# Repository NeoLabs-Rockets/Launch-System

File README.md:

<div align="center">

# NeoLabs-Rockets Launch System

**Rocket systems by NeoLabs — ESP32 launch controller + Node.js mission dashboard.**

---

[🚀 Mission Dashboard](#mission-dashboard) · [🛰️ Launch System](#launch-system)

[Compatible with NeoLabs-Rockets launch platform](https://github.com/NeoLabs-Rockets/Launch-Platform)

---

</div>

## Mission Dashboard

A single-page web app that runs on a laptop at the launch site and connects to a custom PCB over Bluetooth (BLE).

### Features

| Feature | Description |
|---------|-------------|
| **Launch Console** | Guided 4-step wizard: Connect → Checklist → Arm → Countdown. BLE connects once and drives every view. |
| **Live BLE keepalive** | Active ping every 2 s detects silent drops; heartbeat during countdown proves the link every 700 ms. |
| **Weather & airspace** | Live wind, temperature, precipitation, and ADS-B aircraft corridor check with GO / HOLD / NO-GO badge. |
| **Location Finder** | OSM-based candidate scorer — rates grid points against roads, highways (big exclusion), settlements, power lines, water, trees, airports, and open fields. Green-only results on the map; links open Google Earth satellite view. |
| **Camera overlay** | Cinematic broadcast HUD with live T−countdown ring (bottom-right), T+ elapsed after ignition, BLE and weather telemetry. |
| **Cross-device camera** | Phone subscribes to the laptop's SSE stream and receives the countdown + BLE state in real time — no BLE on the phone needed. |

---

## Launch System

BLE launch controller — see [`/LaunchSystem`](LaunchSystem/).

One-layer PCB - no bridges

---

<div align="center">

*Made with ❤️ by [Neo](https://github.com/neooriginal) · [NeoLabs Systems](https://github.com/NeoLabs-Systems)*

</div>

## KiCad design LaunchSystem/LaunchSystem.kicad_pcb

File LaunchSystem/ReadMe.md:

# NeoLabs Rockets â€” ESP32 Mission Control

BLE-controlled trigger/relay switch built on an ESP32. The board exposes only a
Bluetooth Low Energy launch service; the Mission Dashboard provides the shared
**arm â†’ launch** workflow. Designed to run off a portable power supply.

> Firmware: [`Arduino/ESP32_AP_Trigger/ESP32_AP_Trigger.ino`](Arduino/ESP32_AP_Trigger/ESP32_AP_Trigger.ino)
>
> Web Bluetooth requires a Chromium-family browser such as Chrome or Edge on
> localhost/HTTPS. Firefox and Safari do not currently support this control path.

The controller intentionally starts no WiFi access point and serves no embedded
web UI. One authorized dashboard owns BLE while other dashboards synchronize
through the Mission Dashboard server.

## Arduino compile settings

Install the **NimBLE-Arduino** library from the Arduino Library Manager before
compiling. The sketch uses NimBLE instead of the default ESP32 BLE stack because
it is smaller and well suited to the BLE-only controller.

Recommended Arduino IDE board settings:

| Setting | Value |
|---------|-------|
| Board | ESP32 Dev Module or your exact ESP32 board |
| Partition Scheme | Default works; Huge APP (3MB No OTA) gives more headroom |
| Core Debug Level | None |

The current BLE-only sketch compiles on the default ESP32 Dev Module partition
with NimBLE-Arduino installed. If future features push it over the limit, change
**Tools -> Partition Scheme** to a larger APP partition such as
**Huge APP (3MB No OTA)**.

## Features

- **BLE only** â€” no ESP32 WiFi access point, captive portal, embedded UI, or REST API.
- **Checklist-gated arming** â€” every safety item must be acknowledged before arming.
- **Join authorization** â€” the code exists only in ESP32 firmware. The first BLE-owning
  dashboard needs no code; additional dashboards are verified by the ESP32 through the owner.
- **Lockout** â€” after **10** wrong codes the system locks out until reboot
  (counter is kept in RAM only, so a power cycle clears it).
- **Arm/Disarm safety** â€” the trigger is disabled until the system is armed.
  Auto-disarms after every shot.
- **Launch sequence** â€” 10 s countdown with English browser TTS; says
  *"Ignition"* at zero, then drives the output **HIGH 500 ms later**.
- **Trigger pulse** — non-blocking HIGH pulse on the trigger pin, then back LOW.
- **Status LED** â€” solid while armed, 5 Hz blink while firing.
- **Vibration motor** — distinct haptic patterns for arm, disarm, wrong code, lockout, countdown start, final-second ticks, abort, link-lost safety stop, and ignition. No idle buzz.
- **Physical ARM button** (optional, disabled by default) â€” toggles arm state in hardware.
- **Shared dashboard control** â€” one BLE owner, with status and commands relayed to authorized devices.

## Pin assignments

These are defined at the top of the sketch and are the only place you should
change them:

| Function          | GPIO | Direction        | Notes |
|-------------------|------|------------------|-------|
| **Trigger out**   | `26` | OUTPUT           | Goes HIGH for 2000 ms on launch â†’ relay IN / driver |
| **Status LED**    | `2`  | OUTPUT           | Onboard LED on most DevKits. Set to `-1` to disable |
| **Vibration motor**| `23`| OUTPUT           | Motor **(+)** â†’ GPIO 23, **(â€“)** â†’ GND. Set to `-1` to disable |
| **Physical ARM**  | `25` | INPUT_PULLUP     | Momentary button to **GND** (LOW = pressed). `-1` = disabled (default) |

> âš ï¸ Avoid GPIO 6â€“11 (connected to the SPI flash). GPIO 26 / 25 / 23 / 2 are safe,
> standard output-capable pins on the NodeMCU DevKit.
>
> âš ï¸ Drive the motor through a transistor/MOSFET + flyback diode if it draws more
> than a few mA â€” an ESP32 GPIO can't power a motor directly. A tiny coin/ERM
> motor on a driver board is fine; bare motors need the driver.

## BLE / config

Defined near the top of the sketch:

| Setting      | Default            |
|--------------|--------------------|
| BLE name         | `NeoLabs Launch Controller` |
| Launch code      | `LAUNCH_CODE = "123456"` (stored only in ESP32 firmware) |
| Lockout         | `MAX_ATTEMPTS = 10` wrong codes â†’ locked until reboot |
| Pulse length    | `TRIGGER_MS = 2000` ms |
| Vibration       | Named patterns via `playHaptic(kind)` — non-blocking sequencer, no idle buzz |

## Parts list

| Qty | Part | Note |
|-----|------|------|
| 1 | ESP32 NodeMCU (USB-C) | diymore or similar |
| 1 | 5V 1-channel relay module (opto-isolated) | with screw terminals |
| 1 | 9V battery clip (I-type) | snap-on |
| 1 | Buck converter (9â€“12V â†’ 5V) | or LM7805 + caps |
| 1 set | Dupont jumper wires (M-M + M-F) | â€” |
| 2â€“4 | Alligator clip leads | for the output |
| 1 | Optional: toggle/momentary switch | hardware arming button |
| 1 | Optional: LED + 220Î© resistor | status / continuity |

**Approx. cost:** ~â‚¬15â€“25

## Wiring

### Power
- **9V battery +** â†’ buck converter **IN (+)**
- **9V battery â€“** â†’ buck converter **GND**
- Buck **OUT 5V** â†’ ESP32 **VIN**
- Buck **OUT GND** â†’ ESP32 **GND** + relay **GND**

### Relay control
- ESP32 **GPIO 26** (trigger out) â†’ relay **IN**
- ESP32 **GND** â†’ relay **GND**

### Optional physical ARM button
- ESP32 **GPIO 25** â†’ one leg of the button
- Other leg of the button â†’ ESP32 **GND**
  *(uses the internal pull-up; pressing pulls the pin LOW)*

### Optional status LED
- ESP32 **GPIO 2** â†’ LED **anode** â†’ 220Î© resistor â†’ ESP32 **GND**
  *(GPIO 2 already has the onboard LED on most DevKits)*

### Vibration motor
- Motor **(+)** â†’ ESP32 **GPIO 23**
- Motor **(â€“)** â†’ ESP32 **GND**
  *(For anything bigger than a tiny coin motor, drive it via a transistor/MOSFET
  with a flyback diode rather than straight off the GPIO.)*

### Load output (relay side)
- **9V battery +** â†’ relay **COM**
- Relay **NO** â†’ output alligator clip (+)
- **9V battery â€“** â†’ output alligator clip (â€“)

## REST API

Base URL: `http://192.168.4.1`

| Method | Endpoint                  | Response |
|--------|---------------------------|----------|
| `GET`  | `/api/status`             | `{ "armed", "trigger_active", "uptime_ms", "clients" }` |
| `POST` | `/api/arm?code=123456`    | `{ "ok": true, "armed": true }` â€” `401` invalid code (`attempts_left`), `423` locked out |
| `POST` | `/api/disarm`             | `{ "ok": true, "armed": false }` |
| `POST` | `/api/trigger`            | `{ "ok": true }` â€” or `403 {"ok":false,"error":"not armed"}` |
| `POST` | `/api/buzz?ms=120`        | `{ “ok”: true }` — single haptic pulse of `ms` duration |

`/api/status` also reports `locked` and `attempts_left`. Arming requires the
6-digit global password; triggering requires the system to be armed first:

```bash
curl -X POST "http://192.168.4.1/api/arm?code=123456"
curl -X POST  http://192.168.4.1/api/trigger
curl          http://192.168.4.1/api/status
```

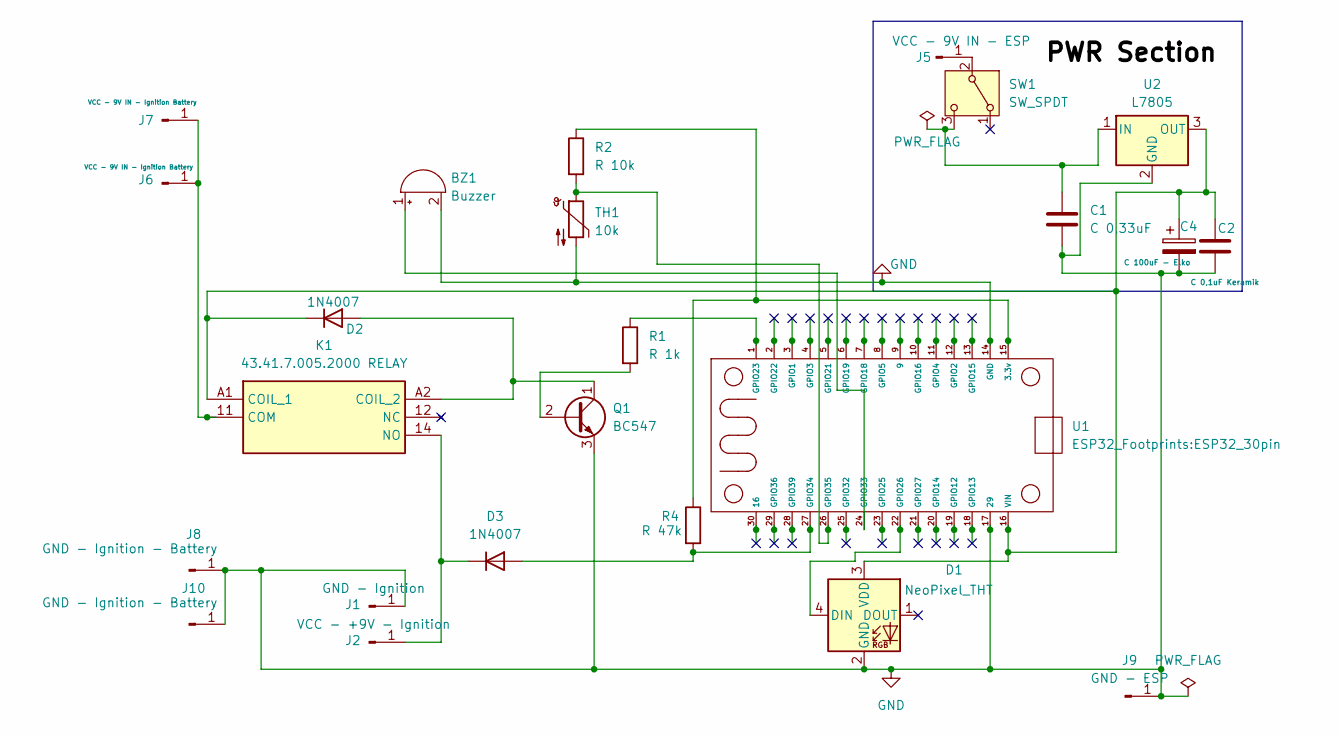
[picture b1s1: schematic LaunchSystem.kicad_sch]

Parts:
BZ1: Buzzer; Buzzer_12x9.5RM7.6
C1: C 0,33uF; C_Disc_D5.0mm_W2.5mm_P5.00mm
C2: C 0,1uF Keramik; C_Disc_D5.0mm_W2.5mm_P5.00mm
C4: C 100uF - Elko; CP_Radial_D5.0mm_P2.00mm
D1: NeoPixel_THT; LED_D5.0mm-4_RGB
D2, D3: 1N4007; D_DO-41_SOD81_P10.16mm_Horizontal
J1: GND - Ignition; TestPoint_Pad_2.0x2.0mm
J2: VCC - +9V - Ignition; TestPoint_Pad_2.0x2.0mm
J5: VCC - 9V IN - ESP; TestPoint_Pad_2.0x2.0mm
J6, J7: VCC - 9V IN - Ignition Battery; TestPoint_Pad_2.0x2.0mm
J8, J10: GND - Ignition - Battery; TestPoint_Pad_2.0x2.0mm
J9: GND - ESP; TestPoint_Pad_2.0x2.0mm
K1: 43.41.7.005.2000 RELAY; 434170052000; Manufacturer_Part_Number 43.41.7.005.2000
Q1: BC547; TO-92_Inline
R1: R 1k; R_Axial_DIN0207_L6.3mm_D2.5mm_P7.62mm_Horizontal
R2: R 10k; R_Axial_DIN0207_L6.3mm_D2.5mm_P7.62mm_Horizontal
R4: R 47k; R_Axial_DIN0207_L6.3mm_D2.5mm_P7.62mm_Horizontal
SW1: SW_SPDT; SW_SPDT_CK_JS102011SAQN
TH1: 10k; R_Axial_DIN0204_L3.6mm_D1.6mm_P2.54mm_Vertical
U1: ESP32_30pin
U2: L7805; TO-220-3_Vertical

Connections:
GND: BZ1.2 (-), C1.2, C2.2, C4.2, D1.2 (GND), J1.1 (Pin_1_1), J8.1 (Pin_1_1), J9.1 (Pin_1_1), J10.1 (Pin_1_1), Q1.3 (E), TH1.2, U1.14 (GND), U1.17 (29), U2.2 (GND)
unnamed: BZ1.1 (+), U1.24 (GPIO33)
unnamed: D1.4 (DIN), U1.22 (GPIO26)
unnamed: C2.1, C4.1, D1.3 (VDD), D2.1 (K), K1.A1 (COIL_1), U1.16 (VIN), U2.3 (OUT)
unnamed: D2.2 (A), K1.A2 (COIL_2), Q1.1 (C)
unnamed: D3.2 (A), R4.2, U1.27 (GPIO34)
unnamed: D3.1 (K), J2.1 (Pin_1_1), K1.14 (NO)
unnamed: J5.1 (Pin_1_1), SW1.2 (B)
unnamed: J6.1 (Pin_1_1), J7.1 (Pin_1_1), K1.11 (COM)
unnamed: Q1.2 (B), R1.2
unnamed: C1.1, SW1.3 (C), U2.1 (IN)
unnamed: R2.1, R4.1, U1.15 (3.3v)
unnamed: R1.1, U1.1 (GPIO23)
unnamed: R2.2, TH1.1, U1.26 (GPIO35)

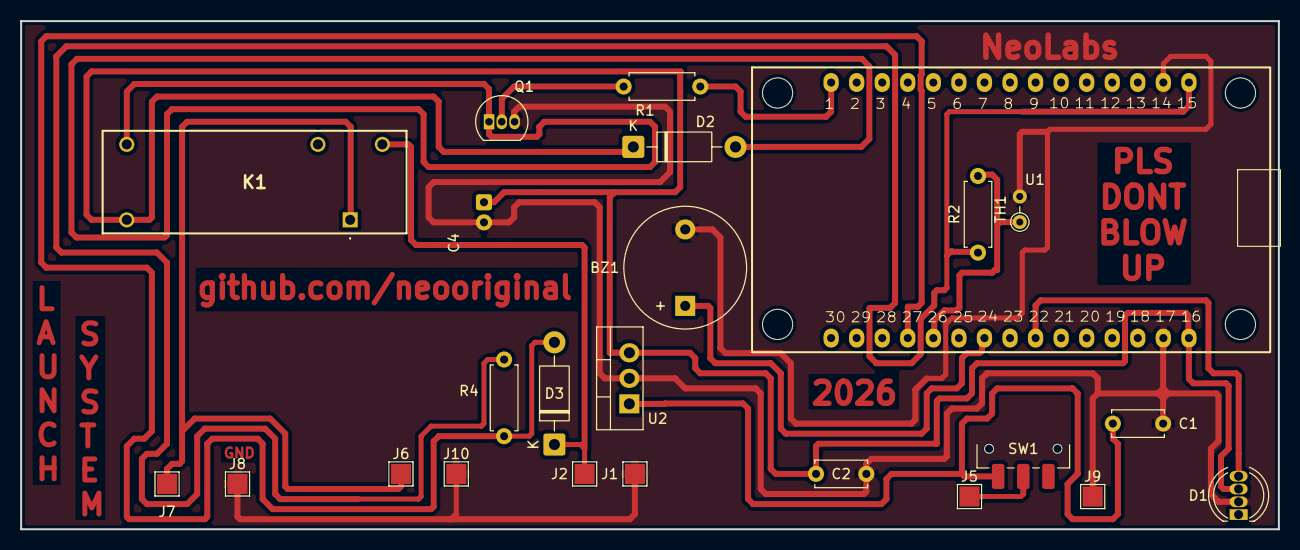
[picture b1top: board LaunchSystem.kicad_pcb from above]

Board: 2 copper layers, 125.0 x 50.5 mm, 24 parts (1 on the bottom side), 14 nets.

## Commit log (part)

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2026-06-21 Initial commit #2
2026-06-22 fix and 3d model
2026-06-22 fixed 3d model
2026-06-22 re-commit
2026-06-22 rename
2026-06-22 Rockets
2026-06-24 update models
2026-06-24 MissionDash
2026-06-26 fixes
2026-06-26 make missiondash more reliable
2026-06-26 revamp exp1
2026-06-27 ui improv
2026-06-28 ping
2026-06-29 improvements
